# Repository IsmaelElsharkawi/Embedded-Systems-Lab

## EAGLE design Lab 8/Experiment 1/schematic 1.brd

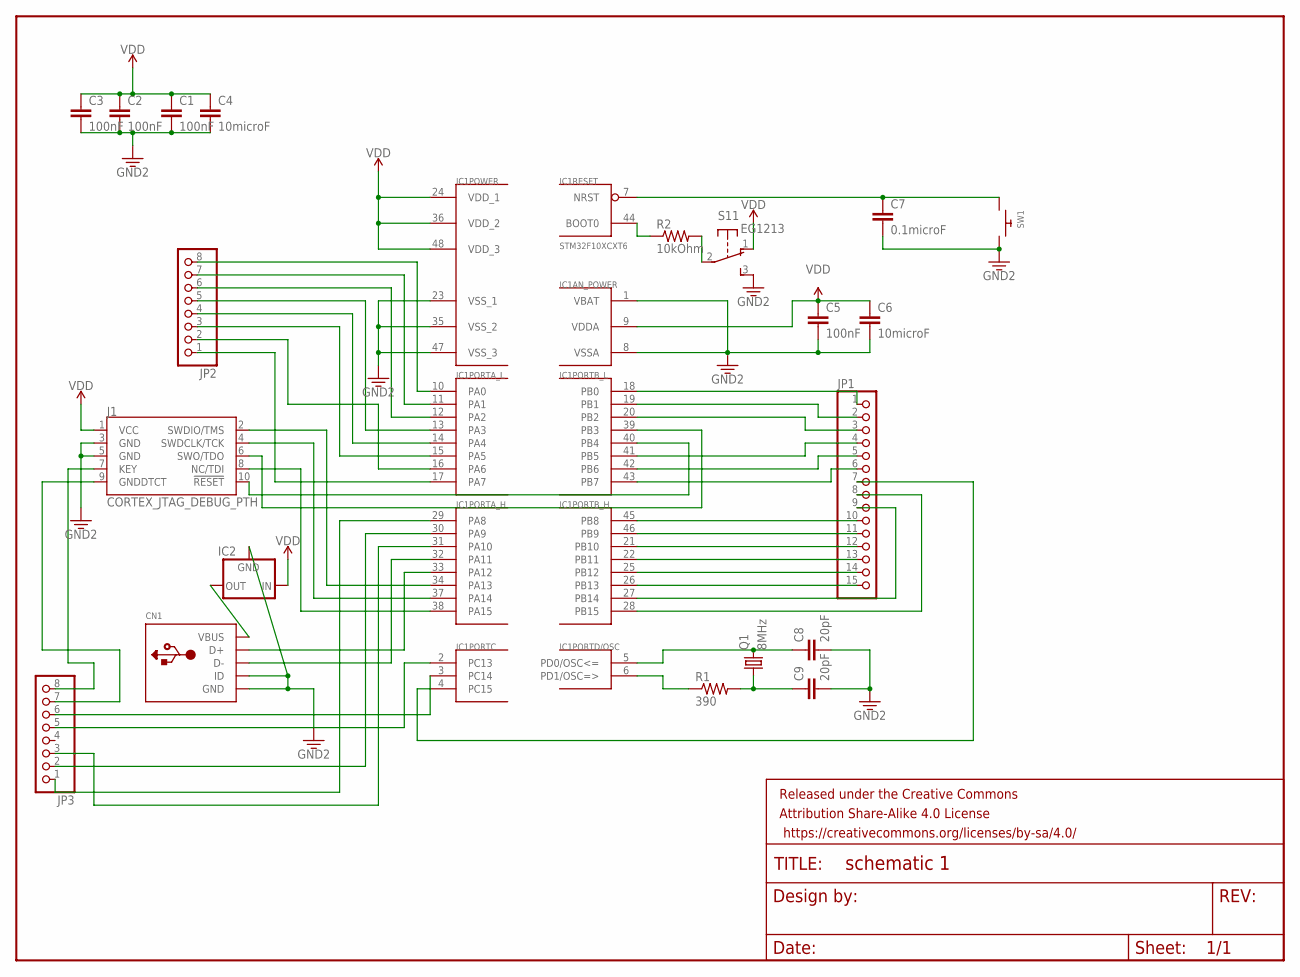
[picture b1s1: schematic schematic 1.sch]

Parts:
C1, C2, C3, C5: 100nF; C2.5-3
C4, C6: 10microF; C2.5-3
C7: 0.1microF; C2.5-3
C8, C9: 20pF; C2.5-3
CN1: USBMINIB; USB-MINIB
FRAME1: FRAME-LETTER; CREATIVE_COMMONS
IC1: STM32F10XCXT6; TQFP48
IC2: MCP1700INLINE; TO92-INLINE
J1: CORTEX_JTAG_DEBUG_PTH; 2X5-PTH-1.27MM
JP1: PINHD-1X15-CB; 1X15-CB
JP2, JP3: PINHD-1X8-3.5MM; 1X08-3.5MM
Q1: 8MHz; 86SMX
R1: 390; 0805-THM
R2: 10kOhm; 0805-THM
S1: EG1213
SW1: SWITCH_PUSHBUTTONEVQ-PE; TACT_PANA-EVQ

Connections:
3.3V: C1.2, C2.2, C3.2, C4.2, C5.2, C6.2, C7.2, C8.2, C9.2, CN1.GND, CN1.ID, IC1.1 (VBAT), IC1.8 (VSSA), IC1.23 (VSS_1), IC1.35 (VSS_2), IC1.47 (VSS_3), IC2.1 (GND), J1.3 (GND), J1.5 (GND), S1.3 (S), SW1.P$2
unnamed: C7.1, IC1.7 (NRST), SW1.P$1
unnamed: C8.1, IC1.5 (PD0/OSC<=), Q1.4 (2)
unnamed: IC1.44 (BOOT0), R2.1
unnamed: C9.1, Q1.1, R1.2
unnamed: IC1.6 (PD1/OSC=>), R1.1
unnamed: R2.2, S1.2
unnamed: IC1.40 (PB4), J1.10 (!RESET)
unnamed: IC1.38 (PA15), J1.8 (NC/TDI)
unnamed: IC1.10 (PA0), JP2.8
unnamed: IC1.37 (PA14), J1.4 (SWDCLK/TCK)
unnamed: IC1.39 (PB3), J1.6 (SWO/TDO)
unnamed: CN1.D+, IC1.33 (PA12)
unnamed: CN1.D-, IC1.32 (PA11)
unnamed: CN1.VBUS, IC2.3 (OUT)
unnamed: IC1.18 (PB0), JP1.1
unnamed: IC1.19 (PB1), JP1.2
unnamed: IC1.20 (PB2), JP1.3
unnamed: IC1.41 (PB5), JP1.4
unnamed: IC1.42 (PB6), JP1.5
unnamed: IC1.43 (PB7), JP1.6
unnamed: IC1.45 (PB8), JP1.10
unnamed: IC1.46 (PB9), JP1.11
unnamed: IC1.21 (PB10), JP1.12
unnamed: IC1.22 (PB11), JP1.13
unnamed: IC1.25 (PB12), JP1.14
unnamed: IC1.26 (PB13), JP1.15
unnamed: IC1.27 (PB14), JP1.9
unnamed: IC1.28 (PB15), JP1.8
unnamed: IC1.4 (PC15), JP1.7
unnamed: IC1.34 (PA13), J1.2 (SWDIO/TMS)
unnamed: IC1.11 (PA1), JP2.7
unnamed: IC1.12 (PA2), JP2.6
unnamed: IC1.13 (PA3), JP2.5
unnamed: IC1.14 (PA4), JP2.4
unnamed: IC1.15 (PA5), JP2.3
unnamed: IC1.16 (PA6), JP2.2
unnamed: IC1.17 (PA7), JP2.1
unnamed: J1.7 (KEY), JP3.8
unnamed: J1.9 (GNDDTCT), JP3.7
unnamed: IC1.29 (PA8), JP3.1
unnamed: IC1.30 (PA9), JP3.2
unnamed: IC1.31 (PA10), JP3.3
unnamed: IC1.3 (PC14), JP3.6
unnamed: IC1.2 (PC13), JP3.5
VDD: C1.1, C2.1, C3.1, C4.1, C5.1, C6.1, IC1.9 (VDDA), IC1.24 (VDD_1), IC1.36 (VDD_2), IC1.48 (VDD_3), IC2.2 (IN), J1.1 (VCC), S1.1 (O)

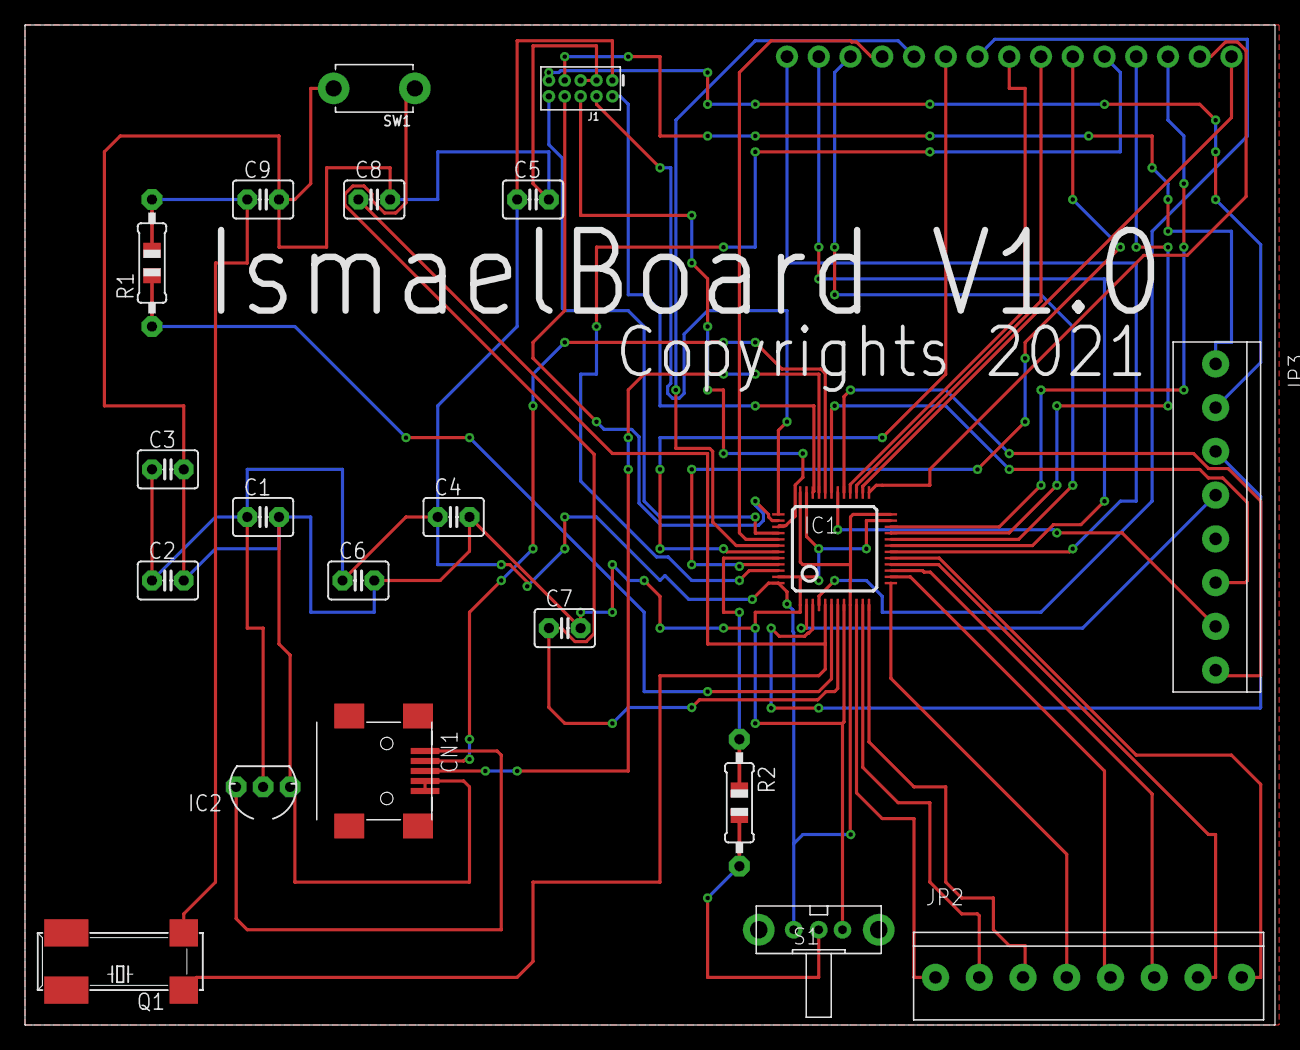
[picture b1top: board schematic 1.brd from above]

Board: 2 copper layers, 100.0 x 80.0 mm, 22 parts (0 on the bottom side), 46 nets.

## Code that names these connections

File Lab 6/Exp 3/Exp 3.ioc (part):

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Mcu.Name=STM32L432K(B-C)Ux
Mcu.Package=UFQFPN32
Mcu.UserName=STM32L432KCUx
PA1.Mode=Full_Duplex_Master
PA1.Signal=SPI1_SCK
PA10.Mode=Asynchronous
PA10.Signal=USART1_RX
PA13\ (JTMS-SWDIO).Mode=Serial_Wire
PA13\ (JTMS-SWDIO).Signal=SYS_JTMS-SWDIO
PA14\ (JTCK-SWCLK).Mode=Serial_Wire
PA14\ (JTCK-SWCLK).Signal=SYS_JTCK-SWCLK
PA2.Signal=GPIO_Output
PA6.Mode=Full_Duplex_Master
PA6.Signal=SPI1_MISO
PA7.Mode=Full_Duplex_Master
PA7.Signal=SPI1_MOSI
PA9.Mode=Asynchronous
PA9.Signal=USART1_TX
PB3\ (JTDO-TRACESWO).Mode=Full_Duplex_Slave
PB3\ (JTDO-TRACESWO).Signal=SPI3_SCK
PB4\ (NJTRST).Mode=Full_Duplex_Slave
PB4\ (NJTRST).Signal=SPI3_MISO
PB5.Mode=Full_Duplex_Slave
PB5.Signal=SPI3_MOSI
PC14-OSC32_IN\ (PC14).Mode=LSE-External-Oscillator
PC14-OSC32_IN\ (PC14).Signal=RCC_OSC32_IN
PC15-OSC32_OUT\ (PC15).Mode=LSE-External-Oscillator
PC15-OSC32_OUT\ (PC15).Signal=RCC_OSC32_OUT
RCC.HSE_VALUE=8000000
RCC.SYSCLKFreq_VALUE=4000000
board=custom

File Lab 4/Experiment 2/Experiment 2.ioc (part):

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Mcu.Name=STM32L432K(B-C)Ux
Mcu.Package=UFQFPN32
Mcu.UserName=STM32L432KCUx
PA13\ (JTMS-SWDIO).Mode=Serial_Wire
PA13\ (JTMS-SWDIO).Signal=SYS_JTMS-SWDIO
PA14\ (JTCK-SWCLK).Mode=Serial_Wire
PA14\ (JTCK-SWCLK).Signal=SYS_JTCK-SWCLK
PA2.Mode=Asynchronous
PA2.Signal=USART2_TX
PA3.Mode=Asynchronous
PA3.Signal=USART2_RX
PB3\ (JTDO-TRACESWO).Signal=GPIO_Output
PB6.Mode=Asynchronous
PB6.Signal=USART1_TX
PB7.Mode=Asynchronous
PB7.Signal=USART1_RX
PC14-OSC32_IN\ (PC14).Mode=LSE-External-Oscillator
PC14-OSC32_IN\ (PC14).Signal=RCC_OSC32_IN
PC15-OSC32_OUT\ (PC15).Mode=LSE-External-Oscillator
PC15-OSC32_OUT\ (PC15).Signal=RCC_OSC32_OUT
RCC.HSE_VALUE=8000000
RCC.SYSCLKFreq_VALUE=4000000
board=custom

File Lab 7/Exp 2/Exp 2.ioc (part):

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Mcu.Name=STM32L432K(B-C)Ux
Mcu.Package=UFQFPN32
Mcu.UserName=STM32L432KCUx
PA11.GPIOParameters=GPIO_Label
PA11.GPIO_Label=Trig
PA11.Signal=GPIO_Output
PA13\ (JTMS-SWDIO).Mode=Serial_Wire
PA13\ (JTMS-SWDIO).Signal=SYS_JTMS-SWDIO
PA14\ (JTCK-SWCLK).Mode=Serial_Wire
PA14\ (JTCK-SWCLK).Signal=SYS_JTCK-SWCLK
PA2.Mode=Asynchronous
PA2.Signal=USART2_TX
PA3.Mode=Asynchronous
PA3.Signal=USART2_RX
PA8.Signal=S_TIM1_CH1
PC14-OSC32_IN\ (PC14).Mode=LSE-External-Oscillator
PC14-OSC32_IN\ (PC14).Signal=RCC_OSC32_IN
PC15-OSC32_OUT\ (PC15).Mode=LSE-External-Oscillator
PC15-OSC32_OUT\ (PC15).Signal=RCC_OSC32_OUT
RCC.HSE_VALUE=8000000
RCC.SYSCLKFreq_VALUE=8000000
board=custom

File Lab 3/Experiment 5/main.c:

/* Receive characters from phone using UART1 and send it to PC using UART0 */
#include "TM4C123GH6PM.h"
void UART0Tx(char c);
int main(void)
{
	SYSCTL->RCGCUART |= 3; /* provide clock to UART0 and UART1*/
	SYSCTL->RCGCGPIO |= 3; /* enable clock to PORTA and PORTB */
	SYSCTL->RCGCGPIO |= 0x20; /* enable clock to PORTF */

	/* UART0 initialization */
	UART0->CTL = 0; /* disable UART0 */
	UART0->IBRD = 104; /* 16MHz/(16*9600 baud rate) = 104.1666666666 */
	UART0->FBRD = 11; /* fraction part= 0.1666666*64+0.5 = 11.1666666 */
	UART0->CC = 0; /* use system clock */
	UART0->LCRH = 0x60; /* 8-bit, no parity, 1-stop bit, no FIFO */
	UART0->IM |= 0x0010; /* enable RX interrupt */
	UART0->CTL = 0x301; /* enable UART0, TXE, RXE */
	/* UART1 initialization */
	UART1->CTL = 0; /* disable UART1 */
	UART1->IBRD = 104; /* 16MHz/(16*9600 baud rate) = 104.1666666666 */
	UART1->FBRD = 11; /* fraction part= 0.1666666*64+0.5 = 11.1666666 */
	UART1->CC = 0; /* use system clock */
	UART1->LCRH = 0x60; /* 8-bit, no parity, 1-stop bit, no FIFO */
	UART1->IM |= 0x0010; /* enable RX interrupt */
	UART1->CTL = 0x301; /* enable UART1, TXE, RXE */
	/* UART0 TX0 and RX0 use PA1 and PA0. Set them up. */
	GPIOA->DEN = 0x03; /* Make PA0 and PA1 as digital */
	GPIOA->AFSEL = 0x03; /* Use PA0,PA1 alternate function */
	GPIOA->PCTL = 0x11; /* configure PA0 and PA1 for UART */

	GPIOF->DIR = 0x0E; /* configure Port F to control the LEDs */
	GPIOF->DEN = 0x0E;
	GPIOF->DATA = 0; /* turn LEDs off */
	/* UART1 TX0 and RX0 use PB1 and PB0. Set them up. */
	GPIOB->DEN = 0x03; /* Make PB0 and PB1 as digital */
	GPIOB->AFSEL = 0x03; /* Use PB0,PB1 alternate function */
	GPIOB->PCTL = 0x11; /* configure PB0 and PB1 for UART */

	/* enable interrupt in NVIC and set priority to 3 */
	NVIC->IP[6] = 3 << 5; /* set interrupt no 6 priority to 3 */
	NVIC->ISER[0] |= 0x00000040; /* enable IRQ6 for UART1 */
	__enable_irq(); /* global enable IRQs */
/* provide clock to UART0 */
	
/* enable clock to PORTA */
/* provide clock to UART1 */
/* enable clock to PORTB */
/* enable clock to PORTF */
/* UART0 initialization */
/* UART0 TX0 and RX0 use PA1 and PA0. Set them up. */
/* UART1 initialization, enabling RX interrupt */
/* UART1 TX0 and RX0 use PB1 and PB0. Set them up. */
/* configure Port F pins 3,2,1 to control the LEDs */
/* enable UART1 interrupt in NVIC and set priority to 3 */
/* global enable IRQs */
 while (1) {}
}
void UART1_Handler(void)
{
 volatile int readback;
 char c;
 if (UART1->MIS & 0x0010) /* if a receive interrupt has occurred */
 {
	 c = UART1->DR; /* read the received data */
	 if(c=='r') GPIOF->DATA = 2;
	 if(c=='g') GPIOF->DATA = 8;
	 if(c=='b') GPIOF->DATA = 4;
	 //GPIOF->DATA = c << 1; /* shift left and write it to LEDs */
	 
	 UART1->ICR = 0x0010; /* clear Rx interrupt flag */
	 readback = UART1->ICR; /* a read to force clearing of interrupt flag */
	 UART0Tx(c);
 }
 else
 {
	 /* should not get here. But if it does, */
	 UART1->ICR = UART0->MIS; /* clear all interrupt flags */
	 readback = UART1->ICR; /* a read to force clearing of interrupt flag */
	 }
}
void UART0Tx(char c)
{
 
 //while((UART0->FR & 0x10) != 0){} /* wait until Rx buffer is not empty */
 UART0->DR = c; /* read the received data */
 
}

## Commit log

2021-02-16 Lab0
2021-02-23 Lab1
2021-02-26 Lab 1 with Report Parts
2021-03-09 9March2021
2021-03-15 Lab 3
2021-03-16 Lab 3 Submitted
2021-03-16 Lab(only Experiments)
2021-03-17 New Lab Report
2021-04-06 Lab 4
2021-04-17 Until Lab 7
2021-04-21 Lab 7 Finished
2021-05-11 Lab 8
2021-05-19 Embedded Lab Completed

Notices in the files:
parts and their libraries:
SparkFun-Aesthetics: Licensing: Creative Commons ShareAlike 4.0 International - https://creativecommons.org/licenses/by-sa/4.0
SparkFun-Aesthetics: Released under the Creative Commons Attribution Share-Alike 4.0 License
SparkFun-Aesthetics: https://creativecommons.org/licenses/by-sa/4.0
